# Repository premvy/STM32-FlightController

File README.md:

# ⚡️Custom STM32  Flight Controller

## Description 
This project is a custom designed, two layer flight controller built to serve as the central brain for a drone prototype. The board is driven by an STM32F722RET6 microcontroller, providing the high-speed processing headroom required for low latency PID loops. The hardware stack features an ICM-42688 6-axis IMU, a BMP580 barometer for precision altitude hold, and a dedicated microSD slot for high rate Blackbox data logging. Power delivery is managed through a modern USB-C interface, paired with a BQ series battery management IC and a clean 5V buck-boost circuit to safely drive servos and ESCs. Beyond just getting a vehicle in the air, this board was designed to push a concept from a raw schematic into a fully manufactured physical product.

## PCB design 

_Custom PCB routed in Kicad_

## Schematic

**Hardware Specs:**
* **MCU:** STM32F722RETx clocked by a 25MHz external crystal.
* **Sensors:** ICM-42688 (6-axis IMU) and BMP580 (Barometer).
* **Power:** USB-C connectivity, BQ-series battery charging, a clean 3.3V logic rail, and a 5V buck-boost rail for servos and ESCs.
* **Data Logging:** Dedicated 4-bit microSD slot for high-speed flight recording.
* **I/O:** 3-pin PWM motor headers and hardware `BOOT` / `RESET` buttons.

[View the Bill of Materials (BOM)](./production/bom.md)

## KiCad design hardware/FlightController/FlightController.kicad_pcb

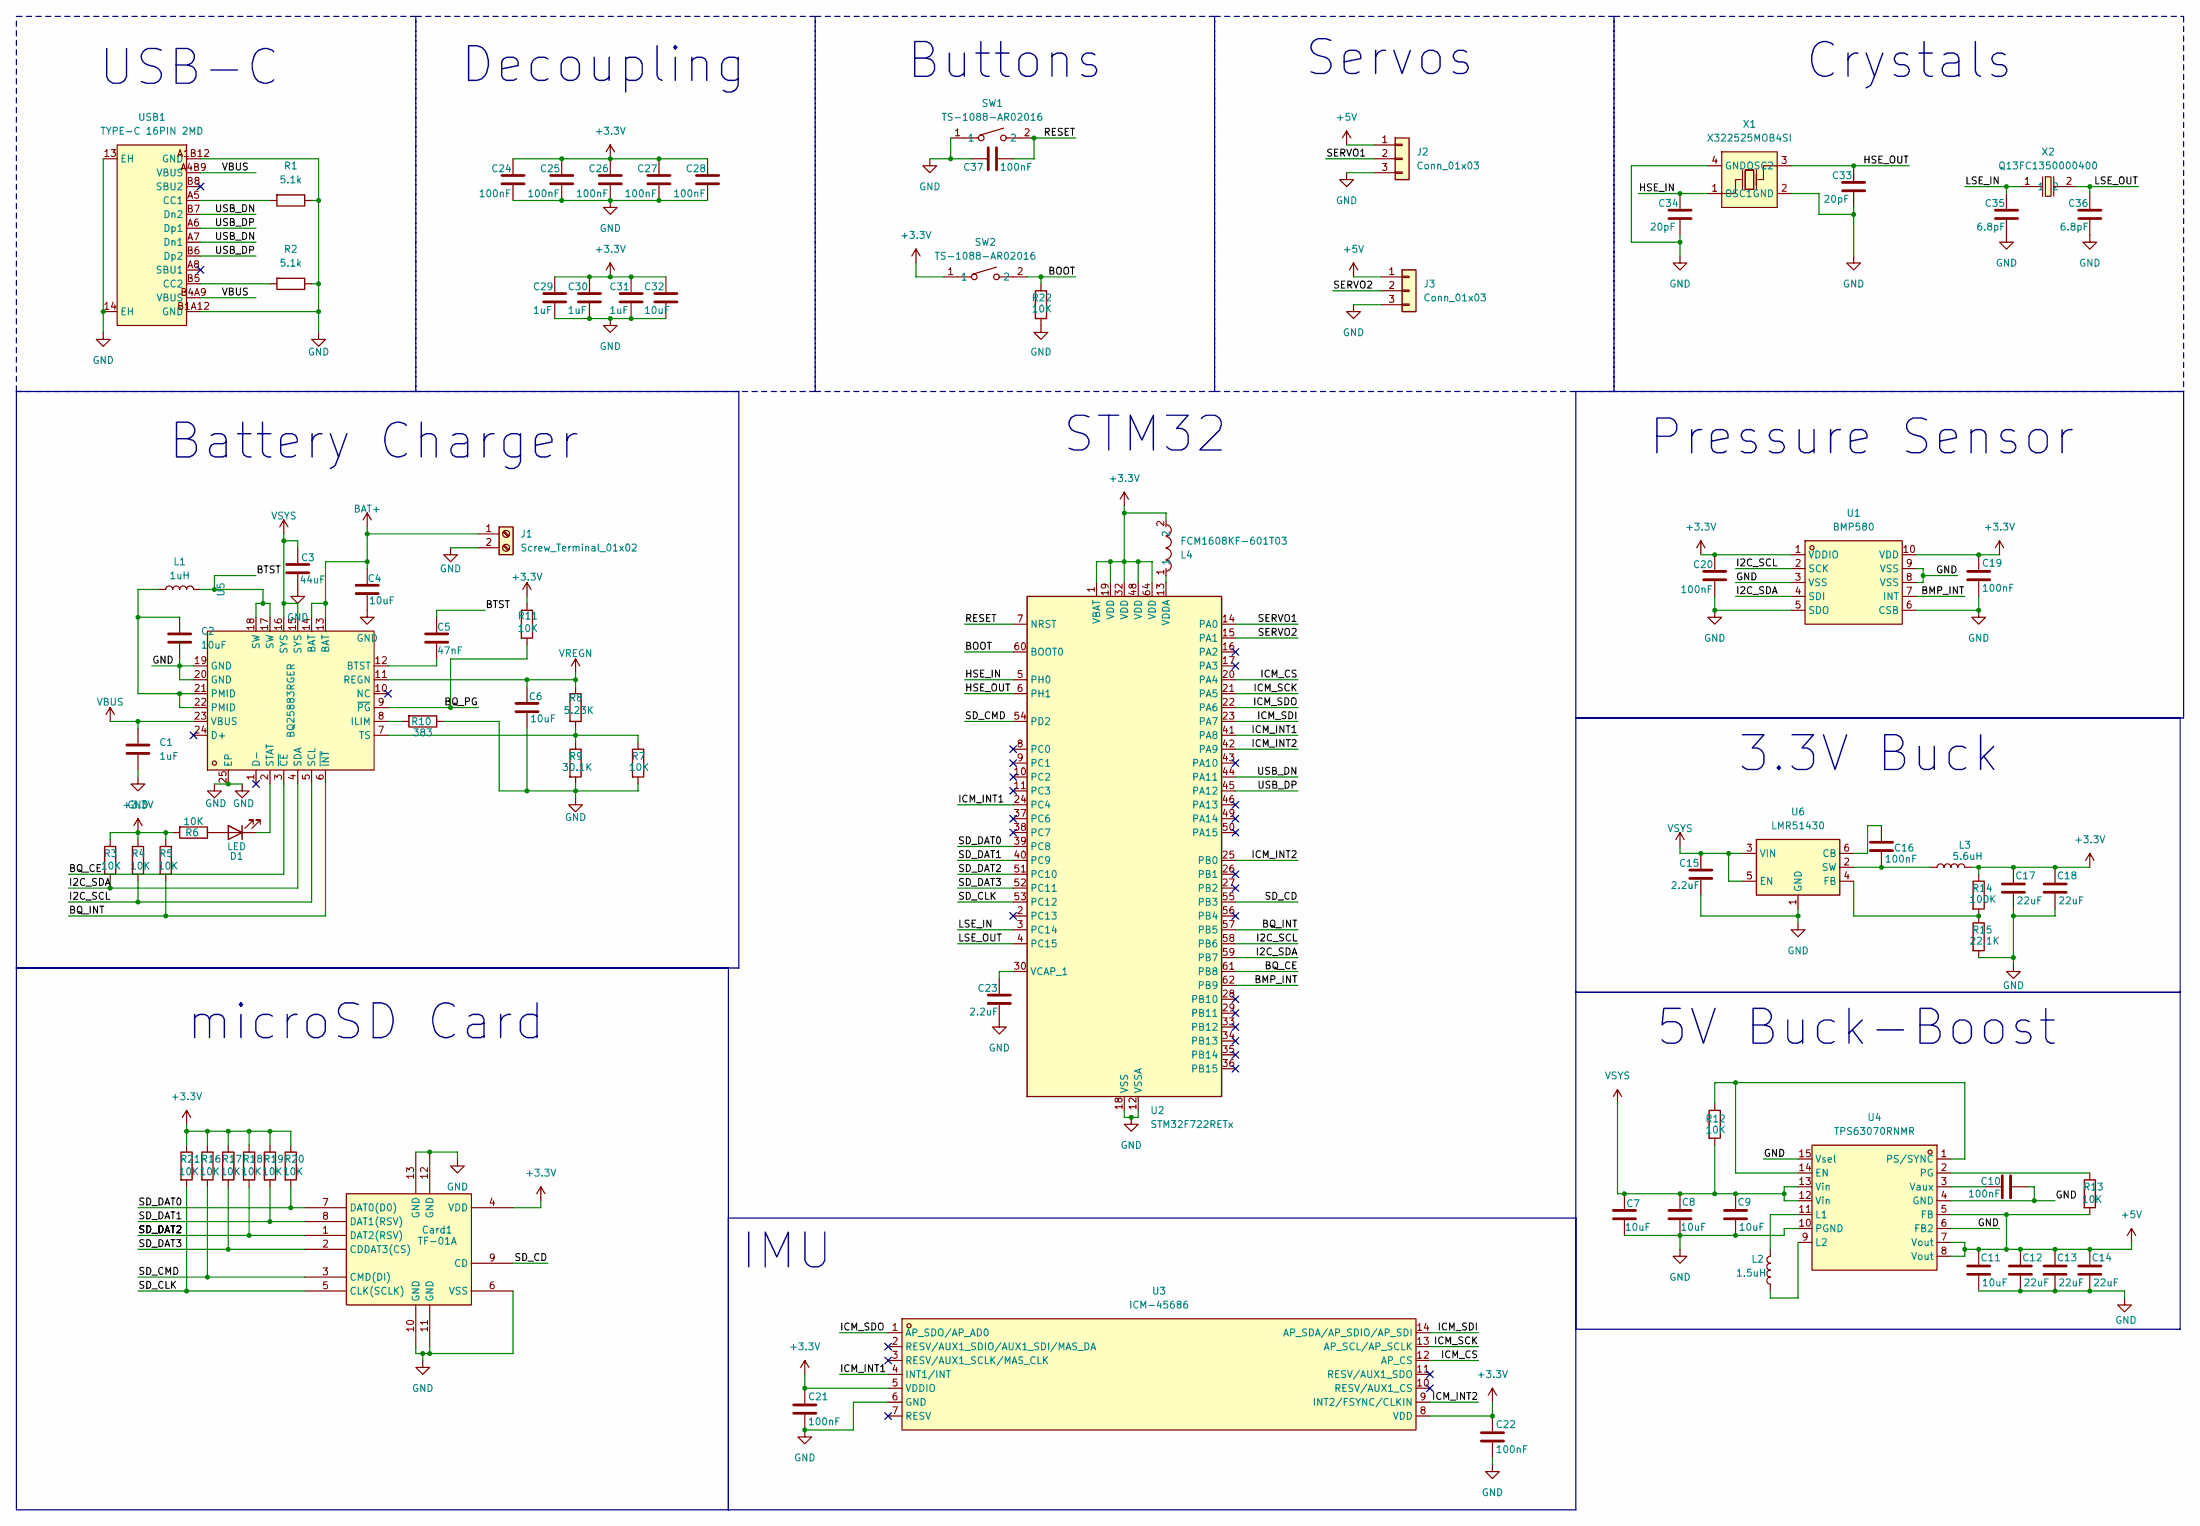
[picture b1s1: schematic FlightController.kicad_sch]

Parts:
C1, C29, C30, C31: 1uF; C_0402_1005Metric
C2, C6, C9, C11: 10uF; C_0603_1608Metric
C3: 44uF; C_0402_1005Metric
C4, C32: 10uF; C_0201_0603Metric
C5: 47nF; C_0402_1005Metric
C7, C8: 10uF; C_0805_2012Metric
C10, C16, C19, C20, C21, C22, C24, C25, C26, C27, C37: 100nF; C_0201_0603Metric
C12, C13, C14: 22uF; C_0805_2012Metric
C15: 2.2uF; C_0603_1608Metric
C17, C18: 22uF; C_0402_1005Metric
C23: 2.2uF; C_0201_0603Metric
C28: 100nF; C_0402_1005Metric
C33, C34: 20pF; C_0201_0603Metric
C35, C36: 6.8pF; C_0201_0603Metric
Card1: TF-01A; TF-SMD_TF-01A; MPN TF-01A; LCSC Part C91145
D1: LED; LED_0402_1005Metric
J1: Screw_Terminal_01x02; TerminalBlock_Xinya_XY308-2.54-2P_1x02_P2.54mm_Horizontal
J2, J3: Conn_01x03; PinHeader_1x03_P2.54mm_Vertical
L1: 1uH; L2520
L2: 1.5uH; IND-SMD_L4.0-W4.0-A
L3: 5.6uH; IND-SMD_L3.0-W3.0
L4: FCM1608KF-601T03; L0603; MPN FCM1608KF-601T03; LCSC Part C141723
R1, R2: 5.1k; R_0201_0603Metric
R3, R4, R5, R6, R7, R11, R12, R13, R16, R17, R18, R19, R20, R21, R22: 10K; R_0201_0603Metric
R8: 5.23K; R_0201_0603Metric
R9: 30.1K; R_0201_0603Metric
R10: 383; R_0201_0603Metric
R14: 100K; R_0402_1005Metric
R15: 22.1K; R_0201_0603Metric
SW1, SW2: TS-1088-AR02016; SW-SMD_L3.9-W3.0-P4.45; MPN TS-1088-AR02016; LCSC Part C720477
U1: BMP580; LGA-10_L2.0-W2.0-P0.50-TL_BMP580; MPN BMP580; LCSC Part C22391138
U2: STM32F722RETx; LQFP-64_10x10mm_P0.5mm
U3: ICM-45686; LGA-14_L3.0-W2.5-P0.50-TL; MPN ICM-45686; LCSC Part C22459454
U4: TPS63070RNMR; VQFN-15_L3.0-W2.5-P0.50-BL; MPN TPS63070RNMR; LCSC Part C109322
U5: BQ25883RGER; VFQFPN-24_L4.0-W4.0-P0.50-BL-EP2.8; MPN BQ25883RGER; LCSC Part C544362
U6: LMR51430; SOT-23-6
USB1: TYPE-C 16PIN 2MD; USB-C-SMD_TYPE-C-16PIN-2MD-073; MPN TYPE-C 16PIN 2MD(073); LCSC Part C2765186
X1: X322525MOB4SI; CRYSTAL-SMD_4P-L3.2-W2.5-BL; MPN X322525MOB4SI; LCSC Part C9006
X2: Q13FC1350000400; FC-135R_L3.2-W1.5; MPN Q13FC13500004; LCSC Part C32346

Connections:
+3.3V: C17.1, C18.1, C19.1, C20.1, C21.1, C22.1, C24.1, C25.1, C26.1, C27.1, C28.1, C29.1, C30.1, C31.1, C32.1, Card1.4 (VDD), L3.2, L4.2, R3.1, R4.1, R5.1, R6.2, R11.1, R14.1, R16.1, R17.1, R18.1, R19.1, R20.1, R21.1, SW2.1, U1.1 (VDDIO), U1.10 (VDD), U2.1 (VBAT), U2.19 (VDD), U2.32 (VDD), U2.48 (VDD), U2.64 (VDD), U3.5 (VDDIO), U3.8 (VDD)
+5V: C11.1, C12.1, C13.1, C14.1, J2.1, J3.1, R13.2, U4.5 (FB), U4.7 (Vout), U4.8 (Vout)
/BMP_INT: U1.7 (INT), U2.62 (PB9)
/BOOT: R22.1, SW2.2, U2.60 (BOOT0)
/BQ_CE: U2.61 (PB8), U5.3 (~CE)
/BQ_INT: R5.2, U2.57 (PB5), U5.6 (~INT)
/BQ_PG: R11.2, U5.9 (~PG)
/BTST: C5.1, L1.2, U5.17 (SW), U5.18 (SW)
/HSE_IN: C34.1, U2.5 (PH0), X1.1 (OSC1)
/HSE_OUT: C33.1, U2.6 (PH1), X1.3 (OSC2)
/I2C_SCL: R4.2, U1.2 (SCK), U2.58 (PB6), U5.5 (SCL)
/I2C_SDA: R3.2, U1.4 (SDI), U2.59 (PB7), U5.4 (SDA)
/ICM_CS: U2.20 (PA4), U3.12 (AP_CS)
/ICM_INT1: U2.24 (PC4), U2.41 (PA8), U3.4 (INT1/INT)
/ICM_INT2: U2.25 (PB0), U2.42 (PA9), U3.9 (INT2/FSYNC/CLKIN)
/ICM_SCK: U2.21 (PA5), U3.13 (AP_SCL/AP_SCLK)
/ICM_SDI: U2.23 (PA7), U3.14 (AP_SDA/AP_SDIO/AP_SDI)
/ICM_SDO: U2.22 (PA6), U3.1 (AP_SDO/AP_AD0)
/LSE_IN: C35.1, U2.3 (PC14), X2.1
/LSE_OUT: C36.1, U2.4 (PC15), X2.2
/RESET: C37.2, SW1.2, U2.7 (NRST)
/SD_CD: Card1.9 (CD), U2.55 (PB3)
/SD_CLK: Card1.5 (CLK(SCLK)), R21.2, U2.53 (PC12)
/SD_CMD: Card1.3 (CMD(DI)), R16.2, U2.54 (PD2)
/SD_DAT0: Card1.7 (DAT0(D0)), R20.2, U2.39 (PC8)
/SD_DAT1: Card1.8 (DAT1(RSV)), R19.2, U2.40 (PC9)
/SD_DAT2: Card1.1 (DAT2(RSV)), R18.2, U2.51 (PC10)
/SD_DAT3: Card1.2 (CDDAT3(CS)), R17.2, U2.52 (PC11)
/SERVO1: J2.2, U2.14 (PA0)
/SERVO2: J3.2, U2.15 (PA1)
/USB_DN: U2.44 (PA11), USB1.A7 (Dn1), USB1.B7 (Dn2)
/USB_DP: U2.45 (PA12), USB1.A6 (Dp1), USB1.B6 (Dp2)
BAT+: C4.1, J1.1, U5.13 (BAT), U5.14 (BAT)
GND: C1.2, C2.2, C3.2, C4.2, C6.2, C7.2, C8.2, C9.2, C10.1, C11.2, C12.2, C13.2, C14.2, C15.2, C17.2, C18.2, C19.2, C20.2, C21.2, C22.2, C23.2, C24.2, C25.2, C26.2, C27.2, C28.2, C29.2, C30.2, C31.2, C32.2, C33.2, C34.2, C35.2, C36.2, C37.1, Card1.6 (VSS), Card1.10 (GND), Card1.11 (GND), Card1.12 (GND), Card1.13 (GND), J1.2, J2.3, J3.3, R1.1, R2.1, R7.2, R9.2, R10.1, R15.2, R22.2, SW1.1, U1.3 (VSS), U1.5 (SDO), U1.6 (CSB), U1.8 (VSS), U1.9 (VSS), U2.12 (VSSA), U2.18 (VSS), U2.31 (VSS), U2.47 (VSS), U2.63 (VSS), U3.6 (GND), U4.4 (GND), U4.6 (FB2), U4.10 (PGND), U4.15 (Vsel), U5.19 (GND), U5.20 (GND), U5.25 (EP), U6.1 (GND), USB1.13 (EH), USB1.14 (EH), USB1.A1B12 (GND), USB1.B1A12 (GND), X1.2 (GND), X1.4 (GND)
unnamed: C2.1, L1.1, U5.21 (PMID), U5.22 (PMID)
unnamed: D1.2 (A), R6.1
unnamed: D1.1 (K), U5.2 (STAT)
unnamed: C23.1, U2.30 (VCAP_1)
unnamed: L4.1, U2.13 (VDDA)
unnamed: R12.1, U4.1 (PS/SYNC), U4.14 (EN)
unnamed: L2.2, U4.11 (L1)
unnamed: L2.1, U4.9 (L2)
unnamed: R13.1, U4.2 (PG)
unnamed: C10.2, U4.3 (Vaux)
unnamed: C5.2, U5.12 (BTST)
unnamed: R10.2, U5.8 (ILIM)
unnamed: R7.1, R8.2, R9.1, U5.7 (TS)
unnamed: C16.2, U6.6 (CB)
unnamed: R14.2, R15.1, U6.4 (FB)
unnamed: C16.1, L3.1, U6.2 (SW)
unnamed: R1.2, USB1.A5 (CC1)
unnamed: R2.2, USB1.B5 (CC2)
VBUS: C1.1, U5.23 (VBUS), USB1.A4B9 (VBUS), USB1.B4A9 (VBUS)
VREGN: C6.1, R8.1, U5.11 (REGN)
VSYS: C3.1, C7.1, C8.1, C9.1, C15.1, R12.2, U4.12 (Vin), U4.13 (Vin), U5.15 (SYS), U5.16 (SYS), U6.3 (VIN), U6.5 (EN)

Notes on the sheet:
Buttons
USB-C
IMU
STM32
Crystals
Pressure Sensor
Servos
Decoupling
microSD Card
3.3V Buck
Battery Charger
5V Buck-Boost

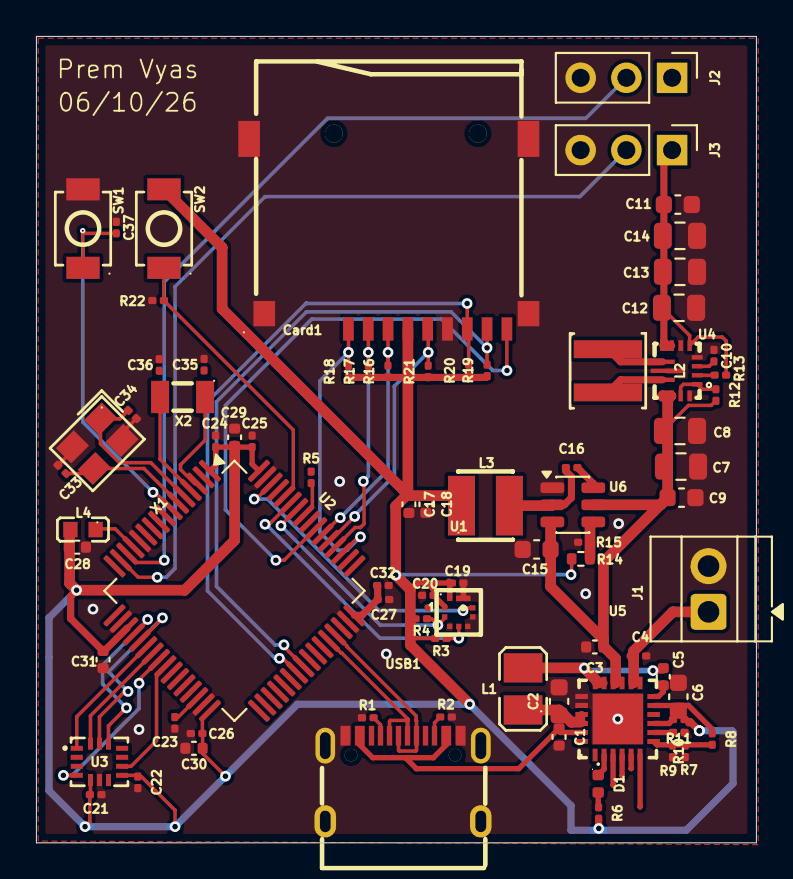
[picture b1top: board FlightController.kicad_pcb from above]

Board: 2 copper layers, 40.0 x 44.8 mm, 79 parts (0 on the bottom side), 55 nets.

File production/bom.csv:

Designator,Footprint,Quantity,Value,LCSC Part #
"C1, C29, C30, C31",0402,4,1uF,
"C10, C16, C19, C20, C21, C22, C24, C25, C26, C27, C37",0201,11,100nF,
"C11, C2, C6, C9",0603,4,10uF,
"C12, C13, C14",0805,3,22uF,
C15,0603,1,2.2uF,
"C17, C18",0402,2,22uF,
C23,0201,1,2.2uF,
C28,0402,1,100nF,
C3,0402,1,44uF,
"C32, C4",0201,2,10uF,
"C33, C34",0201,2,20pF,
"C35, C36",0201,2,6.8pF,
C5,0402,1,47nF,
"C7, C8",0805,2,10uF,
CARD1,TF-SMD_TF-01A,1,TF-01A,C91145
D1,0402,1,LED,
J1,TerminalBlock_Xinya_XY308-2.54-2P_1x02_P2.54mm_Horizontal,1,Screw_Terminal_01x02,
"J2, J3",PinHeader_1x03_P2.54mm_Vertical,2,Conn_01x03,
L1,L2520,1,1uH,C435392
L2,IND-SMD_L4.0-W4.0-A,1,1.5uH,C3033018
L3,IND-SMD_L3.0-W3.0,1,5.6uH,C18236327
L4,L0603,1,FCM1608KF-601T03,C141723
"R1, R2",0201,2,5.1k,
R10,0201,1,383,
"R11, R12, R13, R16, R17, R18, R19, R20, R21, R22, R3, R4, R5, R6, R7",0201,15,10K,
R14,0402,1,100K,
R15,0201,1,22.1K,
R8,0201,1,5.23K,
R9,0201,1,30.1K,
"SW1, SW2",SW-SMD_L3.9-W3.0-P4.45,2,TS-1088-AR02016,C720477
U1,LGA-10_L2.0-W2.0-P0.50-TL_BMP580,1,BMP580,C22391138
U2,LQFP-64_10x10mm_P0.5mm,1,STM32F722RETx,
U3,LGA-14_L3.0-W2.5-P0.50-TL,1,ICM-45686,C22459454
U4,VQFN-15_L3.0-W2.5-P0.50-BL,1,TPS63070RNMR,C109322
U5,VFQFPN-24_L4.0-W4.0-P0.50-BL-EP2.8,1,BQ25883RGER,C544362
U6,SOT-23-6,1,LMR51430,
USB1,USB-C-SMD_TYPE-C-16PIN-2MD-073,1,TYPE-C 16PIN 2MD,C2765186
X1,CRYSTAL-SMD_4P-L3.2-W2.5-BL,1,X322525MOB4SI,C9006
X2,FC-135R_L3.2-W1.5,1,Q13FC1350000400,C32346

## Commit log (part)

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2026-05-06 Create firmware
2026-05-13 Create hardware
2026-05-13 Create ss
2026-05-28 Add schematic section to README
    Added a new section for the schematic in the README.
2026-05-28 Update Schematic section header in README
2026-05-28 Add schematic image to README
2026-05-28 Update schematic image in README
2026-06-10 Add 3D model section and remove BOM
    Updated the README to include a 3D model section with images and removed the Bill of Materials.
2026-06-10 Update PCB design images in README
    Added a new image to the PCB design section of the README.
2026-06-10 Revise project description for clarity and formatting
    Corrected formatting and removed unnecessary commas for clarity.
2026-06-26 Revise production BOM with updated components
    Updated BOM with new component details and pricing.
2026-06-26 Enhance BOM with unit and extended price columns
    Updated BOM to include unit and extended prices for components.
2026-06-26 Rename bom.csv to bom.md
2026-06-26 Restore Bill of Materials and cost details
    Restored the Bill of Materials and Full Prototype Cost sections with updated formatting and details.
